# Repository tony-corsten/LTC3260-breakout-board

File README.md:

# LTC3260-breakout-board
# Overview
The LTC3260 provides a very low noise dual rail for projects requiring very stable supplies (ADCs, op amps). The main difference between the LTC3260 and the LTC3265 is the absense of a boost regulator on the LTC3260, which makes it more suitable for low voltage rails (e.g., a +/- 5V rail from a +9V battery). The negative rail is generated by an inverting charge pump directly on the input voltage. Both outputs can then be used unregulated, or using the built-in LDOs. [You can find the official documentation for the chip here](https://www.analog.com/en/products/ltc3260.html). This is a breakout board made in Kicad with a barrel jack power input [(the PJ-037A)](https://www.digikey.com/product-detail/en/cui-inc/PJ-037A/CP-037A-ND/1644545) and [SMA connectors](https://www.amazon.com/gp/product/B00G94UK74/ref=ppx_yo_dt_b_search_asin_title?ie=UTF8&psc=1) for shielded, low noise power transfer over distance. 

*_Note_*: The board is currently designed for a +/- 5V rail for a 9V battery input. You can adjust the output voltage by tweaking either voltage divider, where the specific formula for output voltage is given on page 10 of the technical manual. 

# Navigating this repo
The main folder contains relevant Kicad files (.pro, .pcb, .sch). The `gerber` directory has a PCB-fabrication ready set of gerber files. The `library` directory contains a custom kicad footprint for the PJ-037A and the SMA connector. 

# Board images
PCB Layout:

Schematic:

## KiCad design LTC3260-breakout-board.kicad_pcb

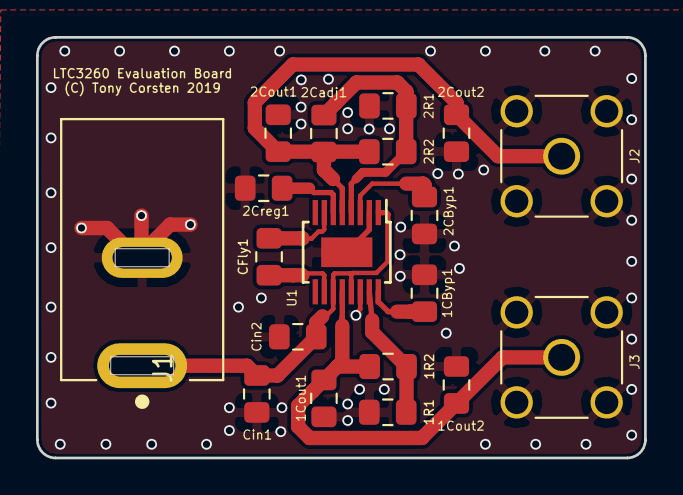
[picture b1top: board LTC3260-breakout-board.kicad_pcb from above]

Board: 2 copper layers, 33.8 x 23.4 mm, 19 parts (0 on the bottom side), 11 nets.

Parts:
1CByp1, 2CByp1: 10nF; C_0805_2012Metric_Pad1.15x1.40mm_HandSolder
1Cout1, 2Cout1, 2Creg1: 10uF; C_0805_2012Metric_Pad1.15x1.40mm_HandSolder
1Cout2, 2Cout2: 0.1uF; C_0805_2012Metric_Pad1.15x1.40mm_HandSolder
1R1, 2R1: 100K; R_0805_2012Metric_Pad1.15x1.40mm_HandSolder
1R2, 2R2: 316K; R_0805_2012Metric_Pad1.15x1.40mm_HandSolder
2Cadj1: 10pF; C_0805_2012Metric_Pad1.15x1.40mm_HandSolder
CFly1: 10uF; C_0805_2012Metric_Pad1.15x1.40mm_HandSolder
Cin1: 10uF; C_0805_2012Metric_Pad1.15x1.40mm_HandSolder
Cin2: 0.1uF; C_0805_2012Metric_Pad1.15x1.40mm_HandSolder
J1: Barrel_Jack; PJ-037A
J2: -5V; SMA_Vertical_Connector
J3: +5V; SMA_Vertical_Connector
U1: LTC3260HMSE-PBF; MSOP-16-1EP_3x4mm_P0.5mm_EP1.65x2.85mm

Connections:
+9V: Cin1.1, Cin2.1, J1.1, U1.1, U1.11, U1.13
/+5V: 1Cout1.1, 1Cout2.1, 1R2.2, J3.1, U1.12
/-5V: 2Cadj1.1, 2Cout1.2, 2Cout2.2, 2R2.2, J2.1, U1.5
GND: 1CByp1.1, 1Cout1.2, 1Cout2.2, 1R1.1, 2CByp1.2, 2Cout1.1, 2Cout2.1, 2Creg1.2, 2R1.2, Cin1.2, Cin2.2, J1.2, J2.2, J3.2, U1.2, U1.14, U1.17
unnamed: 1CByp1.2, U1.16
unnamed: 1R1.2, 1R2.1, U1.15
unnamed: 2CByp1.1, U1.3
unnamed: 2Cadj1.2, 2R1.1, 2R2.1, U1.4
unnamed: 2Creg1.1, U1.6
unnamed: CFly1.1, U1.10
unnamed: CFly1.2, U1.7
